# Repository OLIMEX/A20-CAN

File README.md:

# A20-CAN

CAN driver board for A20-OLinuXino

https://www.olimex.com/wiki/A20-CAN

https://www.olimex.com/Products/OLinuXino/Accessories/A20-CAN/open-source-hardware

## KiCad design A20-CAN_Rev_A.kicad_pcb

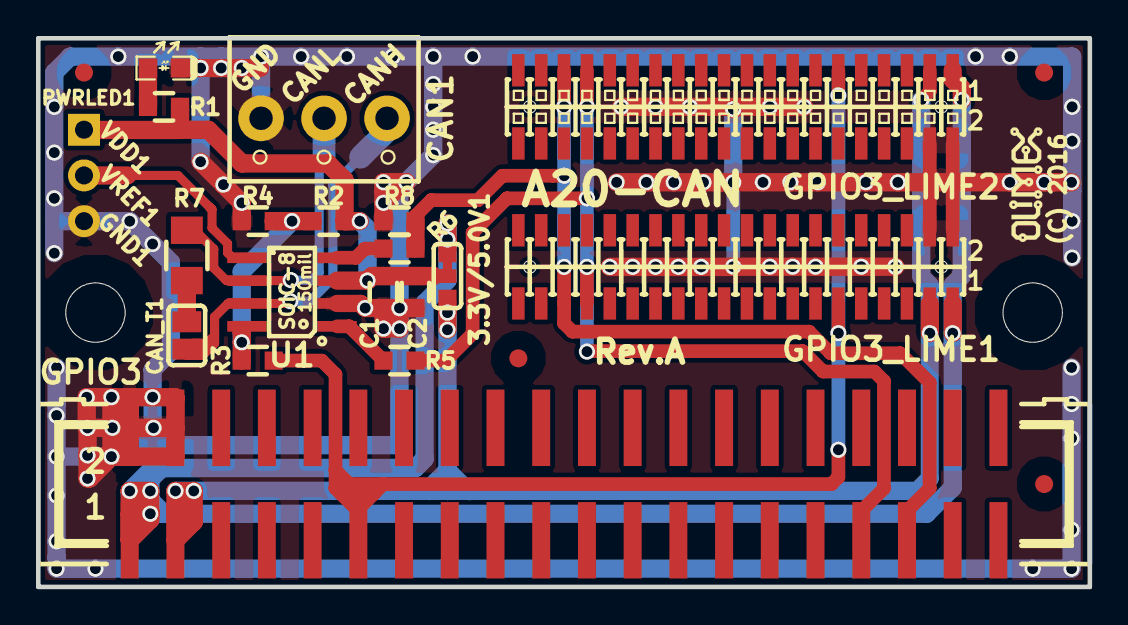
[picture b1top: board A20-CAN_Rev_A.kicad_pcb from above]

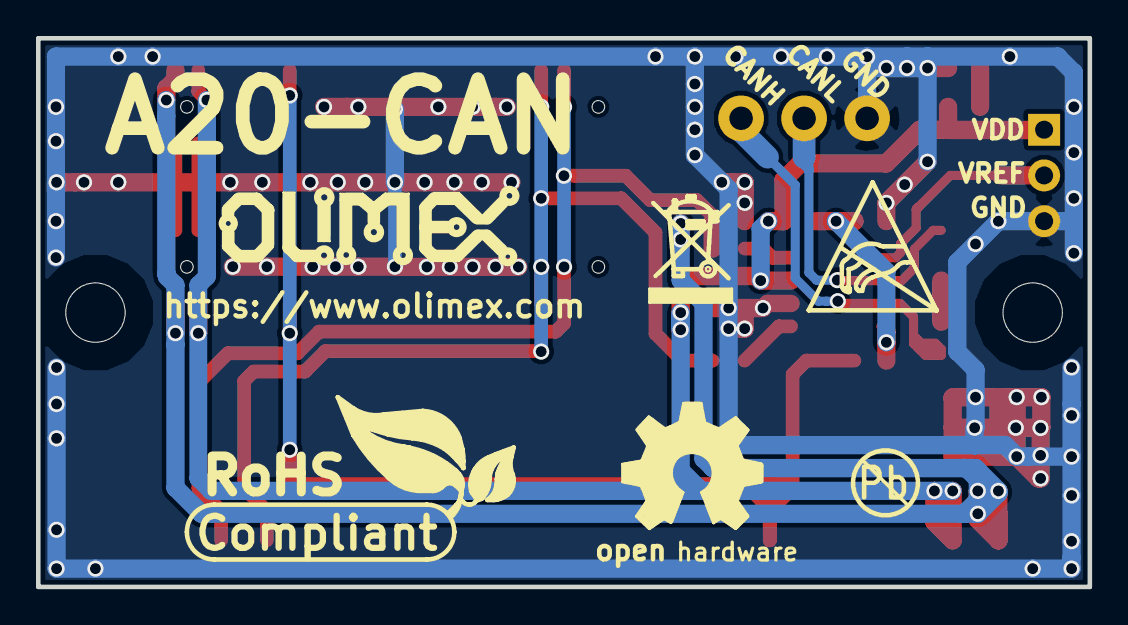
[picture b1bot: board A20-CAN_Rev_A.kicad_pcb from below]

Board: 2 copper layers, 58.4 x 30.5 mm, 25 parts (2 on the bottom side), 15 nets.

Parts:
3.3V/5.0V1: Opened(2-3)/Closed(1-2); SJ_2_SMALL_12_TIED
C1: 100nF; C_0603_5MIL_DWS
C2: 10uF/6.3V/0603; C_0603_5MIL_DWS
CAN1: TB3-3.5mm
CAN_T1: Opened; SJ
GND1: TESTPAD; TEST_PAD_40x70_Round
GPIO3: GBH-254-SMT-40
GPIO3_LIME1: GPH127SMT-02x20; GPCB127SMT-02X20(YA-V36P-2X20-LF)
GPIO3_LIME2: GPH127SMT-02x20; GPH127SMT-02X20(PA-V16X-2X20-LF)
MountingHole: Mounting_hole_3.3mm
MountingHole#2: Mounting_hole_3.3mm
PWRLED1: LED/Red/0603; LED_0603_KA
R1: 2.2k; R_0603_5MIL_DWS
R2: NA; R_0603_5MIL_DWS
R3: NA(330R); R_0603_5MIL_DWS
R4: 10k; R_0603_5MIL_DWS
R5, R6: 330R; R_0603_5MIL_DWS
R7: 120R; R_1206_5MIL_DWS
R8: 680R; R_0603_5MIL_DWS
Ref**: Val**; LOGO_ANTISTATIC_1
Ref**#2: Val**; LOGO_ROHS_1
U1: MCP2551-I/SN(SOIC-8_150mil); SOIC-8_150mil
VDD1: TESTPAD; TEST_PAD40x70_SQUARE
VREF1: TESTPAD; TEST_PAD_40x70_Round

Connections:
+3V3: 3.3V/5.0V1.3, GPIO3.3, GPIO3_LIME1.3, GPIO3_LIME2.3
+5V: 3.3V/5.0V1.1, GPIO3.1, GPIO3_LIME1.1, GPIO3_LIME2.1
/CAN-CTRL: GPIO3.11, GPIO3_LIME1.11, GPIO3_LIME2.11, R3.1
/CAN-RX: GPIO3.35, GPIO3_LIME1.35, GPIO3_LIME2.35, R6.1, R8.2
/CAN-TX: GPIO3.33, GPIO3_LIME1.33, GPIO3_LIME2.33, R5.1
/CANH: CAN1.3, CAN_T1.2, U1.7
/CANL: CAN1.2, R7.2, U1.6
GND: C1.1, C2.1, CAN1.1, GND1.1, GPIO3.2, GPIO3.4, GPIO3_LIME1.2, GPIO3_LIME1.4, GPIO3_LIME2.2, GPIO3_LIME2.4, PWRLED1.1, R4.2, R8.1, U1.2
unnamed: 3.3V/5.0V1.2, C1.2, C2.2, R1.1, R2.2, U1.3, VDD1.1
unnamed: CAN_T1.1, R7.1
unnamed: PWRLED1.2, R1.2
unnamed: R2.1, R3.2, R4.1, U1.8
unnamed: R5.2, U1.1
unnamed: R6.2, U1.4
unnamed: U1.5, VREF1.1

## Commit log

2016-05-24 A20-CAN Rev.A prototype
2019-10-16 Fix
    Wires were missing, fixed pdf.

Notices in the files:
A20-CAN_Rev_A.kicad_pcb:
(C) 2016
